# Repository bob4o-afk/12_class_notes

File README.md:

# **TUTORIAL HOW TO 12 CLASS TUES**:

```plaintext
──────────────────────────────────────────────────────────────
██████╗ ██╗███████╗██╗███████╗██╗  ██╗███╗   ███╗             
██╔══██╗██║██╔════╝██║██╔════╝██║ ██╔╝████╗ ████║             
██████╔╝██║███████╗██║███████╗█████╔╝ ██╔████╔██║             
██╔═══╝ ██║╚════██║██║╚════██║██╔═██╗ ██║╚██╔╝██║             
██║     ██║███████║██║███████║██║  ██╗██║ ╚═╝ ██║             
╚═╝     ╚═╝╚══════╝╚═╝╚══════╝╚═╝  ╚═╝╚═╝     ╚═╝             
──────────────────────────────────────────────────────────────
```

### 💻 **TUES 12th Grade Project** - _"Operation Code"_  
> **⚔️ Welcome to the Digital Frontier! ⚔️**  
Your mission, should you choose to accept it, is to dive into the world of coding and tech innovations. Whether you're using this repo for cheating, revising or learning is your choice!

---

### 🛠️ **Tech Stack**:

- **🔐 Programming Languages**: Everything (which is written and I could copied it)
- **👾 Tools**: Kali Linux, Metasploit, Nmap, Wireshark
- **⚙️ Platforms**: Windows and Linux-based, Cloud Servers, Docker

---

### 🚀 **Installation Guide**:

```bash
# Clone the Repository
git clone https://github.com/bob4o-afk/12_class_notes.git

# Navigate into the Project Directory
cd 12_class_notes
```

---

### 🎯 **If someone asks**:

---

<!-- ### 💾 **Resources**:

- 🖥️ **Operating System**: [Kali Linux](https://www.kali.org/)
- 🔍 **Network Scanning**: [Nmap](https://nmap.org/)
- 📡 **Packet Analysis**: [Wireshark](https://www.wireshark.org/)
- 🔧 **Penetration Testing**: [Metasploit](https://www.metasploit.com/)

--- -->

### 🧑‍💻 **GitHub Stats**:

---

### 🔥 **Contribute to this Project**:

Feel free to contribute by:

1. **Forking** the repo
2. **Creating a new branch** with your cool feature (`git checkout -b feature/YourFeature`)
3. **Committing your changes** (`git commit -m 'Add some stuff'`)
4. **Opening a Pull Request** to merge into the main repository

---

### 🛡️ **Stay Safe Online**:
> “The best defense is a good offense.”

Always remember, with great power comes great responsibility. 

---

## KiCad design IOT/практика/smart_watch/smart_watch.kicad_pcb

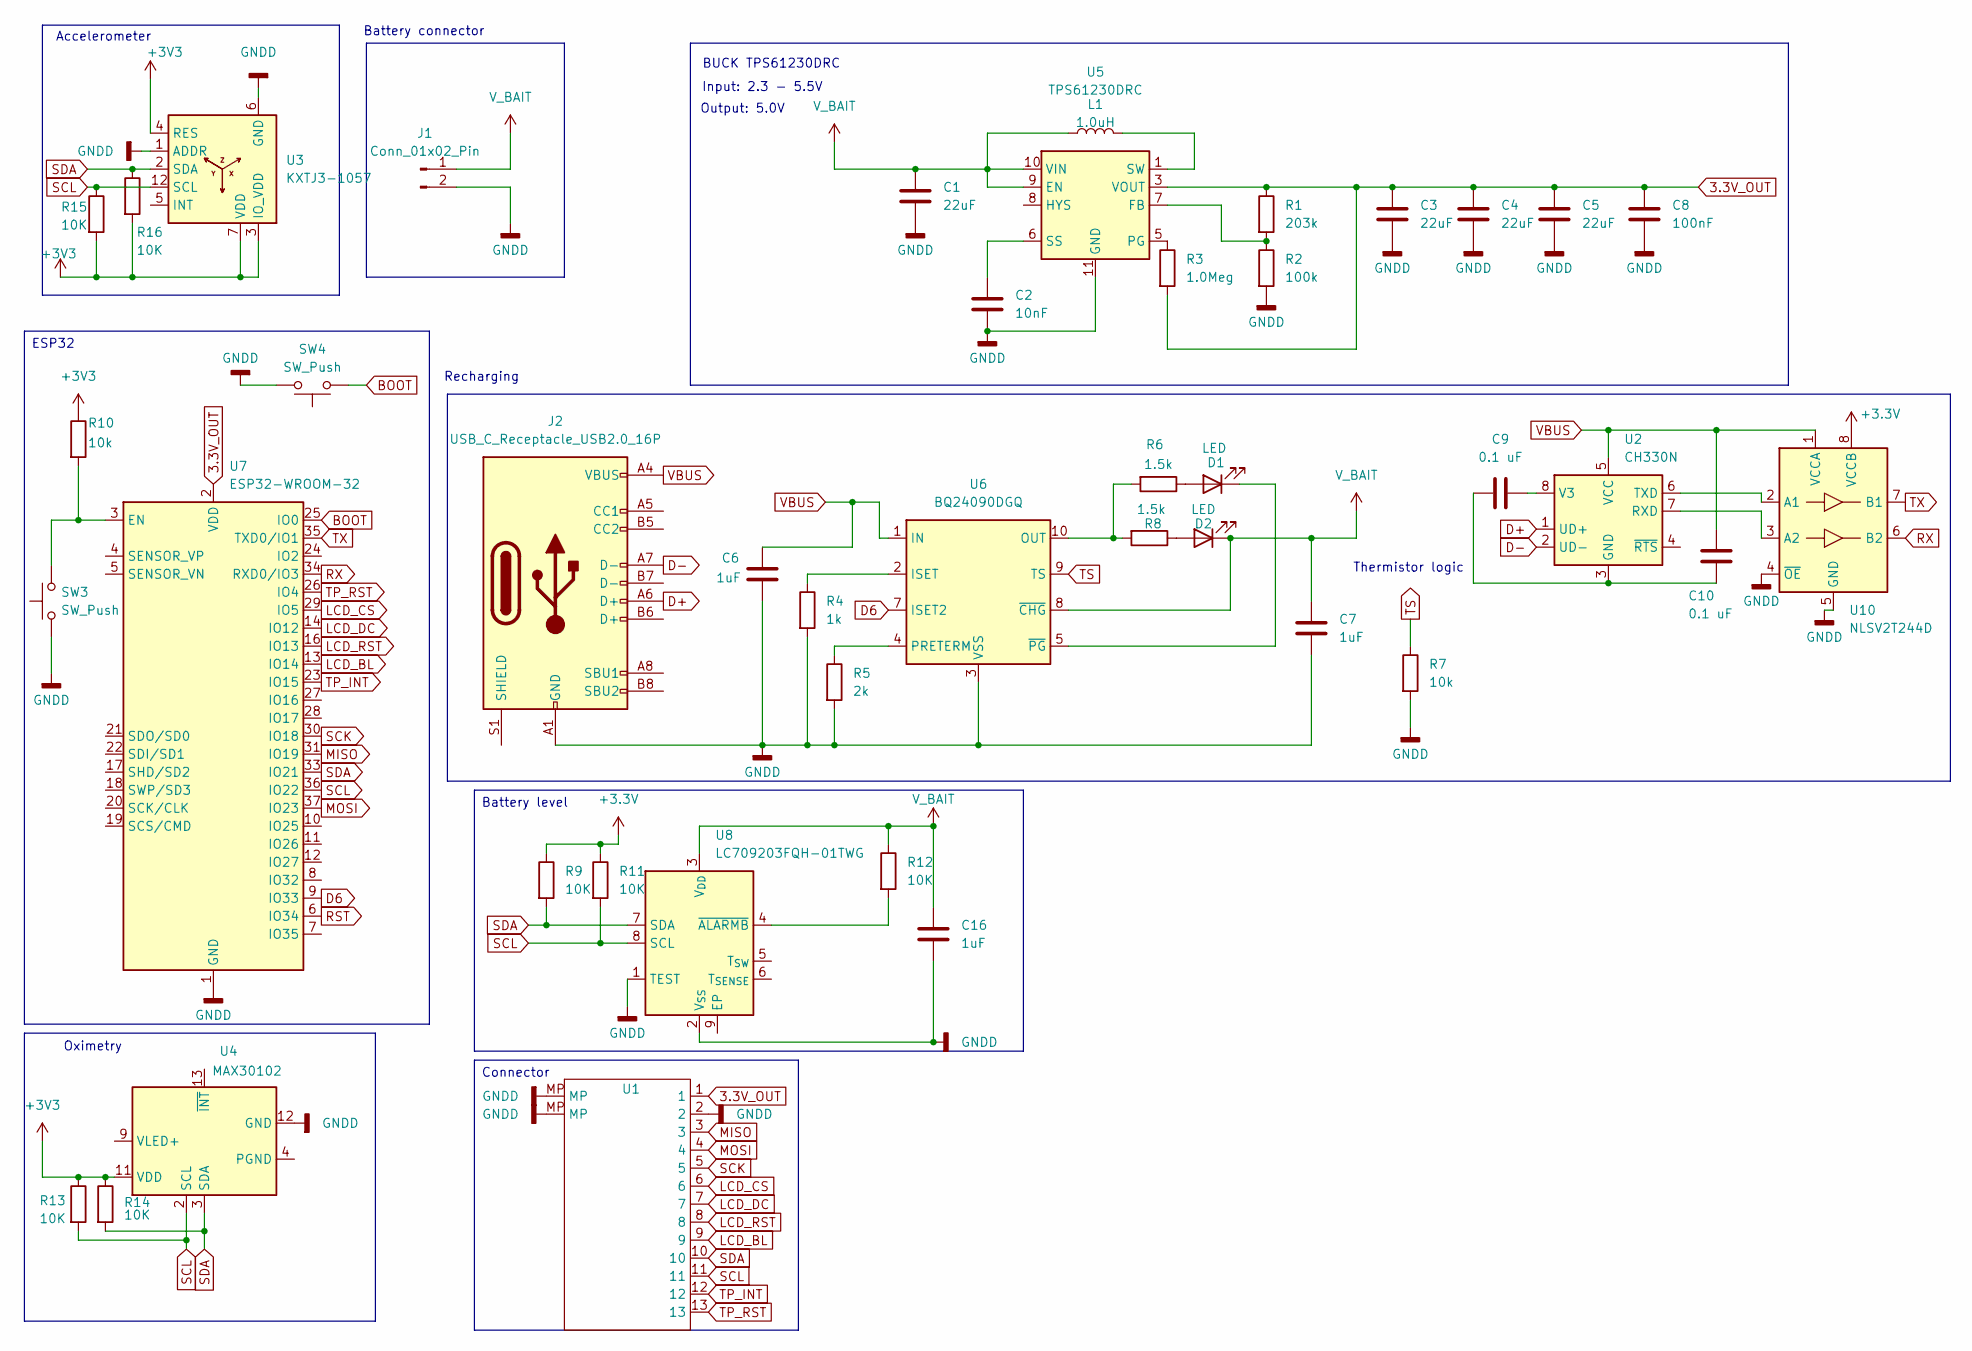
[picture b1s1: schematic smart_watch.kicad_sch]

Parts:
C1, C3, C4, C5: 22uF; C_0603_1608Metric
C2: 10nF; C_0603_1608Metric
C6, C7, C16: 1uF; C_0603_1608Metric
C8: 100nF; C_0603_1608Metric
C9, C10: 0.1 uF; C_0603_1608Metric
D1, D2: LED; LED_0603_1608Metric
J1: Conn_01x02_Pin; TerminalBlock_MaiXu_MX126-5.0-02P_1x02_P5.00mm
J2: USB_C_Receptacle_USB2.0_16P; USB_C_Receptacle_Amphenol_124019772112A
L1: 1.0uH; L_Changjiang_FXL0630
R1: 203k; R_0603_1608Metric
R2: 100k; R_0603_1608Metric
R3: 1.0Meg; R_0603_1608Metric
R4: 1k; R_0603_1608Metric
R5: 2k; R_0603_1608Metric
R6, R8: 1.5k; R_0603_1608Metric
R7, R10: 10k; R_0603_1608Metric
R9, R11, R12, R13, R14, R15, R16: 10K; R_0603_1608Metric
SW3, SW4: SW_Push; SW_Push_1P1T_NO_CK_KMR2
U1: Hirose_FH12-13S-0.5SH_1x13-1MP_P0.50mm_Horizontal
U2: CH330N; SOIC-8_3.9x4.9mm_P1.27mm
U3: KXTJ3-1057; Kionix_LGA-12_2x2mm_P0.5mm_LayoutBorder2x4y
U4: MAX30102; Maxim_OLGA-14_3.3x5.6mm_P0.8mm
U5: TPS61230DRC; Texas_S-PVSON-N10_ThermalVias
U6: BQ24090DGQ; HVSSOP-10-1EP_3x3mm_P0.5mm_EP1.57x1.88mm_ThermalVias
U7: ESP32-WROOM-32
U8: LC709203FQH-01TWG; WDFN-8-1EP_4x3mm_P0.65mm_EP2.4x1.8mm
U10: NLSV2T244D; SOIC-8_3.9x4.9mm_P1.27mm

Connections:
3.3V_OUT: C3.1, C4.1, C5.1, C8.1, R1.1, R3.2, U1.1, U5.3 (VOUT), U5.4 (VOUT), U7.2 (VDD)
+3.3V: R9.1, R11.1, U10.8 (VCCB)
+3V3: R10.1, R13.1, R14.1, R15.2, R16.2, U3.3 (IO_VDD), U3.4 (RES), U3.7 (VDD), U3.10 (VDD), U3.11 (IO_VDD), U4.11 (VDD)
BOOT: SW4.1, U7.25 (IO0)
D6: U6.7 (ISET2), U7.9 (IO33)
D+: J2.A6 (D+), U2.1 (UD+)
D-: J2.A7 (D-), U2.2 (UD-)
GNDD: C1.2, C2.2, C3.2, C4.2, C5.2, C6.2, C7.2, C8.2, C16.2, J1.2, J2.A1 (GND), J2.A12 (GND), J2.B1 (GND), J2.B12 (GND), R2.2, R4.2, R5.2, R7.2, SW3.1, SW4.2, U1.2, U1.MP, U3.1 (ADDR), U3.6 (GND), U3.8 (GND), U3.9 (GND), U4.12 (GND), U5.11 (GND), U6.3 (VSS), U6.11 (VSS), U7.1 (GND), U7.15 (GND), U7.38 (GND), U7.39 (GND), U8.1 (TEST), U8.2 (V_{SS}), U10.4 (~OE), U10.5 (GND)
LCD_BL: U1.9, U7.13 (IO14)
LCD_CS: U1.6, U7.29 (IO5)
LCD_DC: U1.7, U7.14 (IO12)
LCD_RST: U1.8, U7.16 (IO13)
MISO: U1.3, U7.31 (IO19)
MOSI: U1.4, U7.37 (IO23)
unnamed: D1.2 (A), R6.1
unnamed: D1.1 (K), U6.5 (~PG)
unnamed: D2.2 (A), R8.1
unnamed: L1.2, U5.1 (SW), U5.2 (SW)
unnamed: C9.1, C10.2, U2.3 (GND)
unnamed: C9.2, U2.8 (V3)
unnamed: U4.9 (VLED+), U4.10 (VLED+)
unnamed: R1.2, R2.1, U5.7 (FB)
unnamed: R3.1, U5.5 (PG)
unnamed: C2.1, U5.6 (SS)
unnamed: R4.1, U6.2 (ISET)
unnamed: R6.2, R8.2, U6.10 (OUT)
unnamed: R5.1, U6.4 (PRETERM)
unnamed: R10.2, SW3.2, U7.3 (EN)
unnamed: R12.2, U8.4 (~ALARMB)
unnamed: U2.6 (TXD), U10.2 (A1)
unnamed: U2.7 (RXD), U10.3 (A2)
RST: U7.6 (IO34)
RX: U7.34 (RXD0/IO3), U10.6 (B2)
SCK: U1.5, U7.30 (IO18)
SCL: R11.2, R13.2, R15.1, U1.11, U3.12 (SCL), U4.2 (SCL), U7.36 (IO22), U8.8 (SCL)
SDA: R9.2, R14.2, R16.1, U1.10, U3.2 (SDA), U4.3 (SDA), U7.33 (IO21), U8.7 (SDA)
TP_INT: U1.12, U7.23 (IO15)
TP_RST: U1.13, U7.26 (IO4)
TS: R7.1, U6.9 (TS)
TX: U7.35 (TXD0/IO1), U10.7 (B1)
VBUS: C6.1, C10.1, J2.A4 (VBUS), J2.A9 (VBUS), J2.B4 (VBUS), J2.B9 (VBUS), U2.5 (VCC), U6.1 (IN), U10.1 (VCCA)
V_BAIT: C1.1, C7.1, C16.1, D2.1 (K), J1.1, L1.1, R12.1, U5.9 (EN), U5.10 (VIN), U6.8 (~CHG), U8.3 (V_{DD})

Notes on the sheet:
Oximetry
Input: 2.3 - 5.5V
BUCK TPS61230DRC
Recharging
Output: 5.0V
Battery connector
Thermistor logic
Accelerometer
ESP32
Connector
Battery level

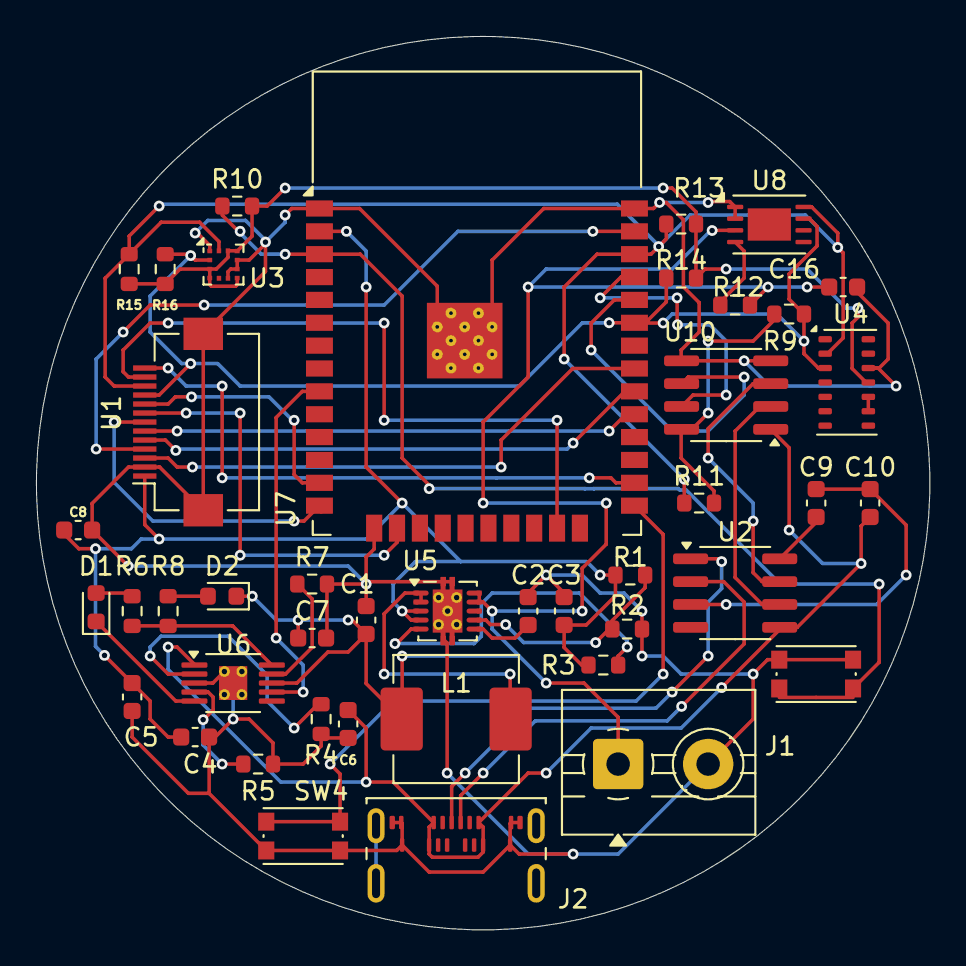
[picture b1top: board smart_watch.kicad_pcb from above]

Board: 2 copper layers, 49.6 x 49.6 mm, 43 parts (0 on the bottom side), 41 nets.

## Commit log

2024-10-06 feat: adding some stuff
2024-10-07 adding hw
2024-10-10 adding stuff from this week
2024-10-11 adding hw for internet programming
2024-10-11 clearing up stuff
2024-10-11 refactoring
2024-10-11 adding files from friday 11.10.24
2024-10-17 adding this week stuff
2024-10-28 adding last week stuff but edited
2024-11-12 05.11 week
2024-11-15 adding stuff
2024-11-19 stuff from 11
2024-11-25 updating stuff
2024-11-29 adding this weeks things 25-29.11.2024
2024-12-01 adding
2024-12-06 updating 6.12.2024 week
2025-02-07 feat: adding some things i dont remember
2025-04-01 feat: adding hws and iot
2025-04-07 feat: adding things
2025-04-22 updating smart watch
